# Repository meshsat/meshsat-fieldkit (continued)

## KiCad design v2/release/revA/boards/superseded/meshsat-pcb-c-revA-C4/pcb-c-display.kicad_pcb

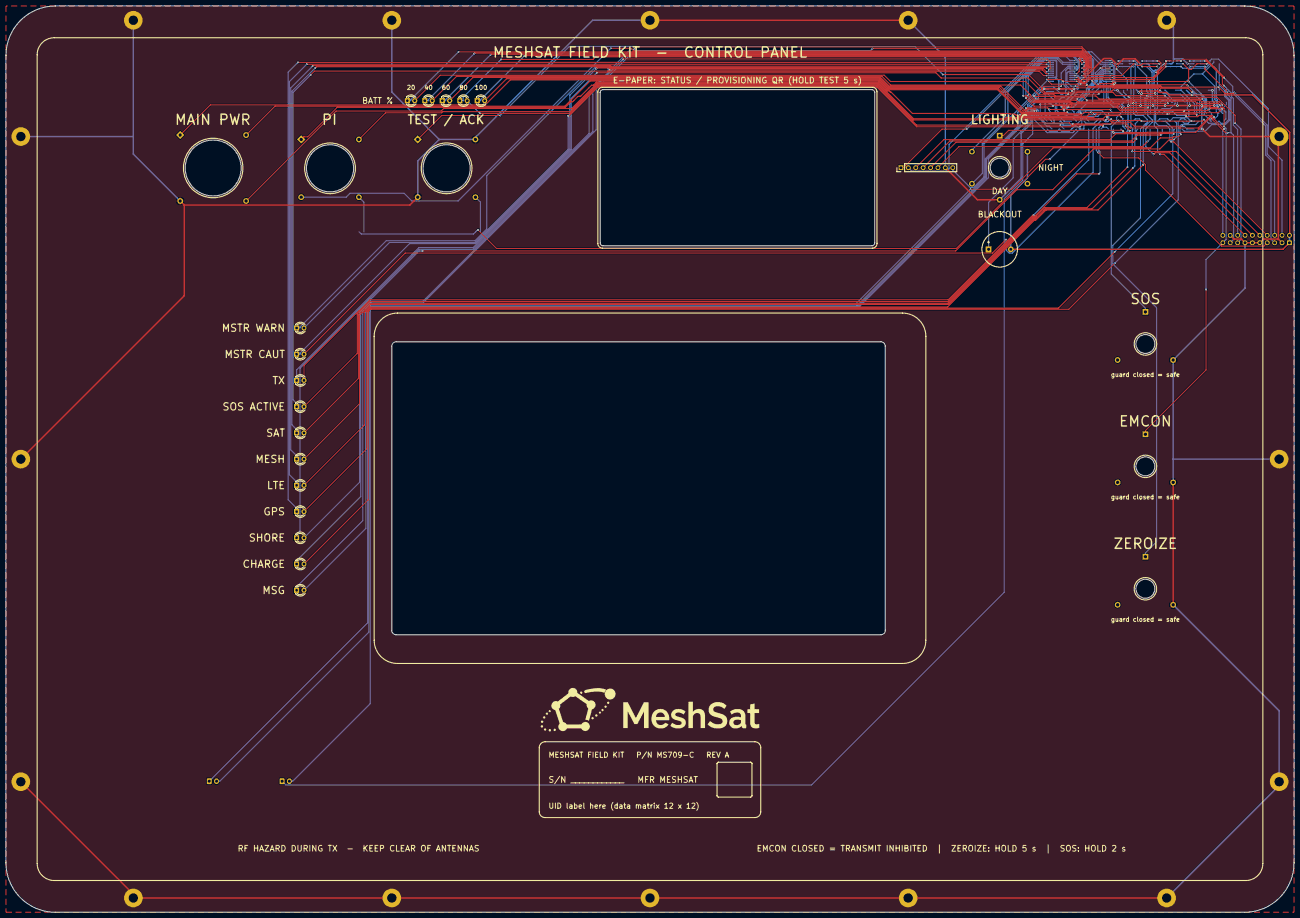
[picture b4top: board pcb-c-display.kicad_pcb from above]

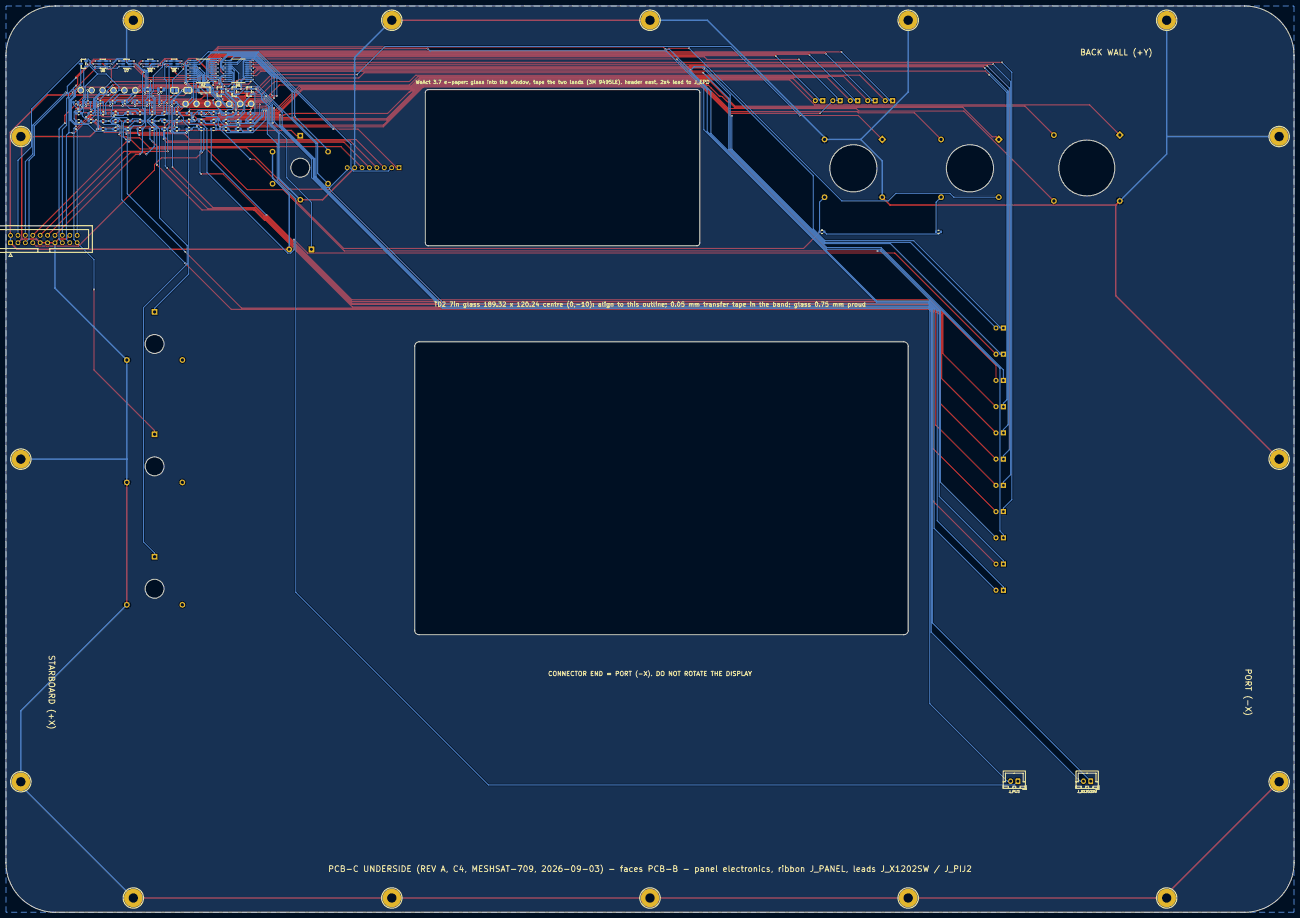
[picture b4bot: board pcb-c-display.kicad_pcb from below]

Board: 2 copper layers, 442.0 x 311.0 mm, 126 parts (85 on the bottom side), 86 nets.

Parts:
BZ1: active piezo 5 V 85 dB; Buzzer_12x9.5RM7.6
C1, C2: 10u; C_0805_2012Metric
C3, C4, C11, C12, C13: 100n; C_0603_1608Metric
C5, C6, C7, C8, C9, C10: 10n; C_0603_1608Metric
D1: 3 mm MWARN red, sunlight viewable; LED_D3.0mm
D2: 3 mm MCAUT amber, sunlight viewable; LED_D3.0mm
D3: 3 mm TX red (RF hazard), sunlight viewable; LED_D3.0mm
D4: 3 mm SOSACT red, sunlight viewable; LED_D3.0mm
D5: 3 mm SAT green, sunlight viewable; LED_D3.0mm
D6: 3 mm MESH green, sunlight viewable; LED_D3.0mm
D7: 3 mm LTE green, sunlight viewable; LED_D3.0mm
D8: 3 mm GPS green, sunlight viewable; LED_D3.0mm
D9: 3 mm SHORE green, sunlight viewable; LED_D3.0mm
D10: 3 mm CHG white, sunlight viewable; LED_D3.0mm
D11: 3 mm MSG white, sunlight viewable; LED_D3.0mm
D12: 3 mm BAT1 amber, sunlight viewable; LED_D3.0mm
D13: 3 mm BAT2 green, sunlight viewable; LED_D3.0mm
D14: 3 mm BAT3 green, sunlight viewable; LED_D3.0mm
D15: 3 mm BAT4 green, sunlight viewable; LED_D3.0mm
D16: 3 mm BAT5 green, sunlight viewable; LED_D3.0mm
D17: BAT54 lamp-test tie; D_SOD-123
FB1, FB2, FB3, FB4: ferrite 600R; L_0603_1608Metric
H1, H2, H3, H4, H5, H6, H7, H8, H9, H10, H11, H12, H13, H14, H15, H16: frame screw M3, GND bond; MountingHole_3.2mm_M3_Pad
JP1: PANEL_ID strap (closed = variant B); SolderJumper-2_P1.3mm_Open_RoundedPad1.0x1.5mm
JP2: EPD RES from BCM7 instead of U2 (close to use); SolderJumper-2_P1.3mm_Open_RoundedPad1.0x1.5mm
J_EPD: e-paper module lead: BUSY RES D/C CS SCL SDA GND 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; PinHeader_1x08_P2.54mm_Vertical
J_PANEL: panel ribbon from PCB-B (IDC 2x10, underside); IDC-Header_2x10_P2.54mm_Vertical
J_PIJ2: lead to the Pi 5 J2 power-button pads (XH2.5); JST_XH_B2B-XH-A_1x02_P2.50mm_Vertical
J_X1202SW: lead to the X1202 external-switch pins (XH2.5); JST_XH_B2B-XH-A_1x02_P2.50mm_Vertical
Q1: AO3401A P-FET high side; SOT-23
Q2, Q3, Q4: 2N7002; SOT-23
R1, R2, R3, R4, R5, R7, R8: 10k; R_0603_1608Metric
R6, R12, R30, R39: 100k; R_0603_1608Metric
R9: 2.2k; R_0603_1608Metric
R10: 47R; R_0603_1608Metric
R11, R34, R35, R36, R37, R38: 100R; R_0603_1608Metric
R13, R14, R15, R23, R28, R32: 300R; R_0603_1608Metric
R16, R17, R18, R19, R20, R21, R22, R24, R25, R26, R27: 180R; R_0603_1608Metric
R29: 1k; R_0603_1608Metric
R31, R33: 470R; R_0603_1608Metric
SW_EMCON: EMCON guarded latching toggle (closed = TX inhibi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; GuardedToggle_SPDT
SW_LIGHT: LIGHTING DAY/NIGHT/BLACKOUT toggle DPDT ON-ON-ON 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; PanelToggle_DPDT
SW_MAIN: MAIN PWR 19 mm momentary, green ring (to X1202 ex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; PanelSwitch_19mm
SW_PI: PI 16 mm recessed momentary, amber ring (to Pi 5 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; PanelSwitch_16mm
SW_SOS: SOS guarded momentary toggle (red cover); GuardedToggle_SPDT
SW_TEST: TEST/ACK 16 mm momentary, white ring; PanelSwitch_16mm
SW_ZERO: ZEROIZE guarded momentary toggle (hold 5 s); GuardedToggle_SPDT
TP1: LED_RAIL; TestPoint_Pad_D1.5mm
TP2: LED_RAIL_SW; TestPoint_Pad_D1.5mm
TP3: +5V; TestPoint_Pad_D1.5mm
TP4: +3V3; TestPoint_Pad_D1.5mm
TP5: GND; TestPoint_Pad_D1.5mm
TP6: EXP_INT; TestPoint_Pad_D1.5mm
TP7: TX_INHIBIT_n; TestPoint_Pad_D1.5mm
TP8: SPARE1; TestPoint_Pad_D1.5mm
TP9: SPARE2; TestPoint_Pad_D1.5mm
TP10: SPARE3; TestPoint_Pad_D1.5mm
TP11: SPARE4; TestPoint_Pad_D1.5mm
TP12: SPARE5; TestPoint_Pad_D1.5mm
TP13: EPD_BUSY; TestPoint_Pad_D1.5mm
U1: PCA9555PW 0x22: LEDs + switches; TSSOP-24_4.4x7.8mm_P0.65mm
U2: PCA9555PW 0x23: LEDs, bar, e-paper control; TSSOP-24_4.4x7.8mm_P0.65mm
U5, U6, U7, U8: USBLC6-2SC6 (2-line TVS); SOT-23-6

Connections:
+3V3: C2.1, C3.1, C4.1, C13.1, J_EPD.8, J_PANEL.20, R1.2, R2.2, R3.2, R4.2, R5.2, R6.2, R8.2, TP4.1, U1.2, U1.24, U2.2, U2.21, U2.24, U5.5, U6.5, U7.5, U8.5
+5V: BZ1.2, C1.1, J_PANEL.1, J_PANEL.2, SW_LIGHT.2, TP3.1
/BAT1_A: D12.2, R23.2
/BAT1_K: D12.1, U2.7
/BAT2_A: D13.2, R24.2
/BAT2_K: D13.1, U2.8
/BAT3_A: D14.2, R25.2
/BAT3_K: D14.1, U2.9
/BAT4_A: D15.2, R26.2
/BAT4_K: D15.1, U2.10
/BAT5_A: D16.2, R27.2
/BAT5_K: D16.1, U2.11
/BZ_K: BZ1.1, Q4.3
/CHG_A: D10.2, R21.2
/CHG_K: D10.1, U1.7
/EPD_BUSY: J_EPD.1, TP13.1, U2.15
/EPD_CS_F: J_EPD.4, R36.2
/EPD_DC: J_PANEL.8, R37.1, U6.3, U6.4
/EPD_DC_F: J_EPD.3, R37.2
/EPD_RES: JP2.2, J_EPD.2, U2.14
/EPD_RES_ALT: JP2.1, J_PANEL.15
/EPD_SCL_F: J_EPD.5, R34.2
/EPD_SDA_F: J_EPD.6, R35.2
/EXP_INT: J_PANEL.6, TP6.1, U1.1, U2.1
/GPS_A: D8.2, R19.2
/GPS_K: D8.1, U1.11
/LED_RAIL: Q1.3, R13.1, R14.1, R15.1, R16.1, R17.1, R18.1, R19.1, R20.1, R21.1, R22.1, R23.1, R24.1, R25.1, R26.1, R27.1, R28.1, R32.1, R33.1, TP1.1
/LED_RAIL_SW: Q1.2, R7.1, R9.1, R31.1, SW_LIGHT.1, TP2.1
/LIGHT_DAY_n: C8.1, R4.1, SW_LIGHT.5, U1.17
/LIGHT_NIGHT_n: C9.1, R5.1, SW_LIGHT.6, U1.18
/LTE_A: D7.2, R18.2
/LTE_K: D7.1, U1.10
/MAINRING_A: R31.2, SW_MAIN.3
/MCAUT_A: D2.2, R14.2
/MCAUT_K: D2.1, U1.6
/MESH_A: D6.2, R17.2
/MESH_K: D6.1, U1.9
/MSG_A: D11.2, R22.2
/MSG_K: D11.1, U2.5
/MWARN_A: D1.2, R13.2
/MWARN_K: D1.1, U1.5
/PANEL_ID: JP1.1, R8.1, U1.20
/PANEL_PWM: J_PANEL.17, R11.1, U8.1, U8.6
/PIJ2_A: FB3.1, SW_PI.1
/PIJ2_A2: C12.1, FB3.2, J_PIJ2.1
/PIJ2_B: FB4.1, SW_PI.2
/PIJ2_B2: C12.2, FB4.2, J_PIJ2.2
/PIRING_A: R32.2, SW_PI.3
/PIRING_K: SW_PI.4, U2.6
/PWM1: J_PANEL.16, R38.1, U8.3, U8.4
/Q1_G: Q1.1, R9.2, R10.1
/Q2_D: Q2.3, R10.2
/Q2_G: Q2.1, R11.2, R12.1
/Q3_G: Q3.1, R29.2, R30.1
/Q4_G: Q4.1, R38.2, R39.1
/RAIL_SENSE: R7.2, U1.19
/SAT_A: D5.2, R16.2
/SAT_K: D5.1, U1.8
/SCL: J_PANEL.5, U1.22, U2.22, U7.3, U7.4
/SDA: J_PANEL.4, U1.23, U2.23, U7.1, U7.6
/SHORE_A: D9.2, R20.2
/SHORE_K: D9.1, U2.4
/SOSACT_A: D4.2, R15.2
/SOSACT_K: D4.1, U1.4
/SOS_SW: C5.1, R1.1, SW_SOS.1, U1.13
/SPARE1: TP8.1, U2.16
/SPARE2: TP9.1, U2.17
/SPARE3: TP10.1, U2.18
/SPARE4: TP11.1, U2.19
/SPARE5: TP12.1, U2.20
/SPI_CE0: J_PANEL.14, R36.1, U6.1, U6.6
/SPI_MOSI: J_PANEL.12, R35.1, U5.3, U5.4
/SPI_SCLK: J_PANEL.10, R34.1, U5.1, U5.6
/TESTRING_A: R33.2, SW_TEST.3
/TEST_SW: C7.1, R3.1, SW_TEST.1, U1.16
/TR_APRS: J_PANEL.7, R29.1
/TX_A: D3.2, R28.2
/TX_INHIBIT_n: C10.1, J_PANEL.19, R6.1, SW_EMCON.1, TP7.1, U1.14
/TX_K: D3.1, D17.2, Q3.3
/TX_LAMPTEST: D17.1, U2.13
/X1202SW_A: FB1.1, SW_MAIN.1
/X1202SW_A2: C11.1, FB1.2, J_X1202SW.1
/X1202SW_B: FB2.1, SW_MAIN.2
/X1202SW_B2: C11.2, FB2.2, J_X1202SW.2
/ZEROIZE_SW: C6.1, R2.1, SW_ZERO.1, U1.15
GND: C1.2, C2.2, C3.2, C4.2, C5.2, C6.2, C7.2, C8.2, C9.2, C10.2, C13.2, H1.1, H2.1, H3.1, H4.1, H5.1, H6.1, H7.1, H8.1, H9.1, H10.1, H11.1, H12.1, H13.1, H14.1, H15.1, H16.1, JP1.2, J_EPD.7, J_PANEL.3, J_PANEL.9, J_PANEL.11, J_PANEL.13, J_PANEL.18, Q2.2, Q3.2, Q4.2, R12.2, R30.2, R39.2, SW_EMCON.2, SW_LIGHT.4, SW_MAIN.4, SW_SOS.2, SW_TEST.2, SW_TEST.4, SW_ZERO.2, TP5.1, U1.3, U1.12, U1.21, U2.3, U2.12, U5.2, U6.2, U7.2, U8.2
